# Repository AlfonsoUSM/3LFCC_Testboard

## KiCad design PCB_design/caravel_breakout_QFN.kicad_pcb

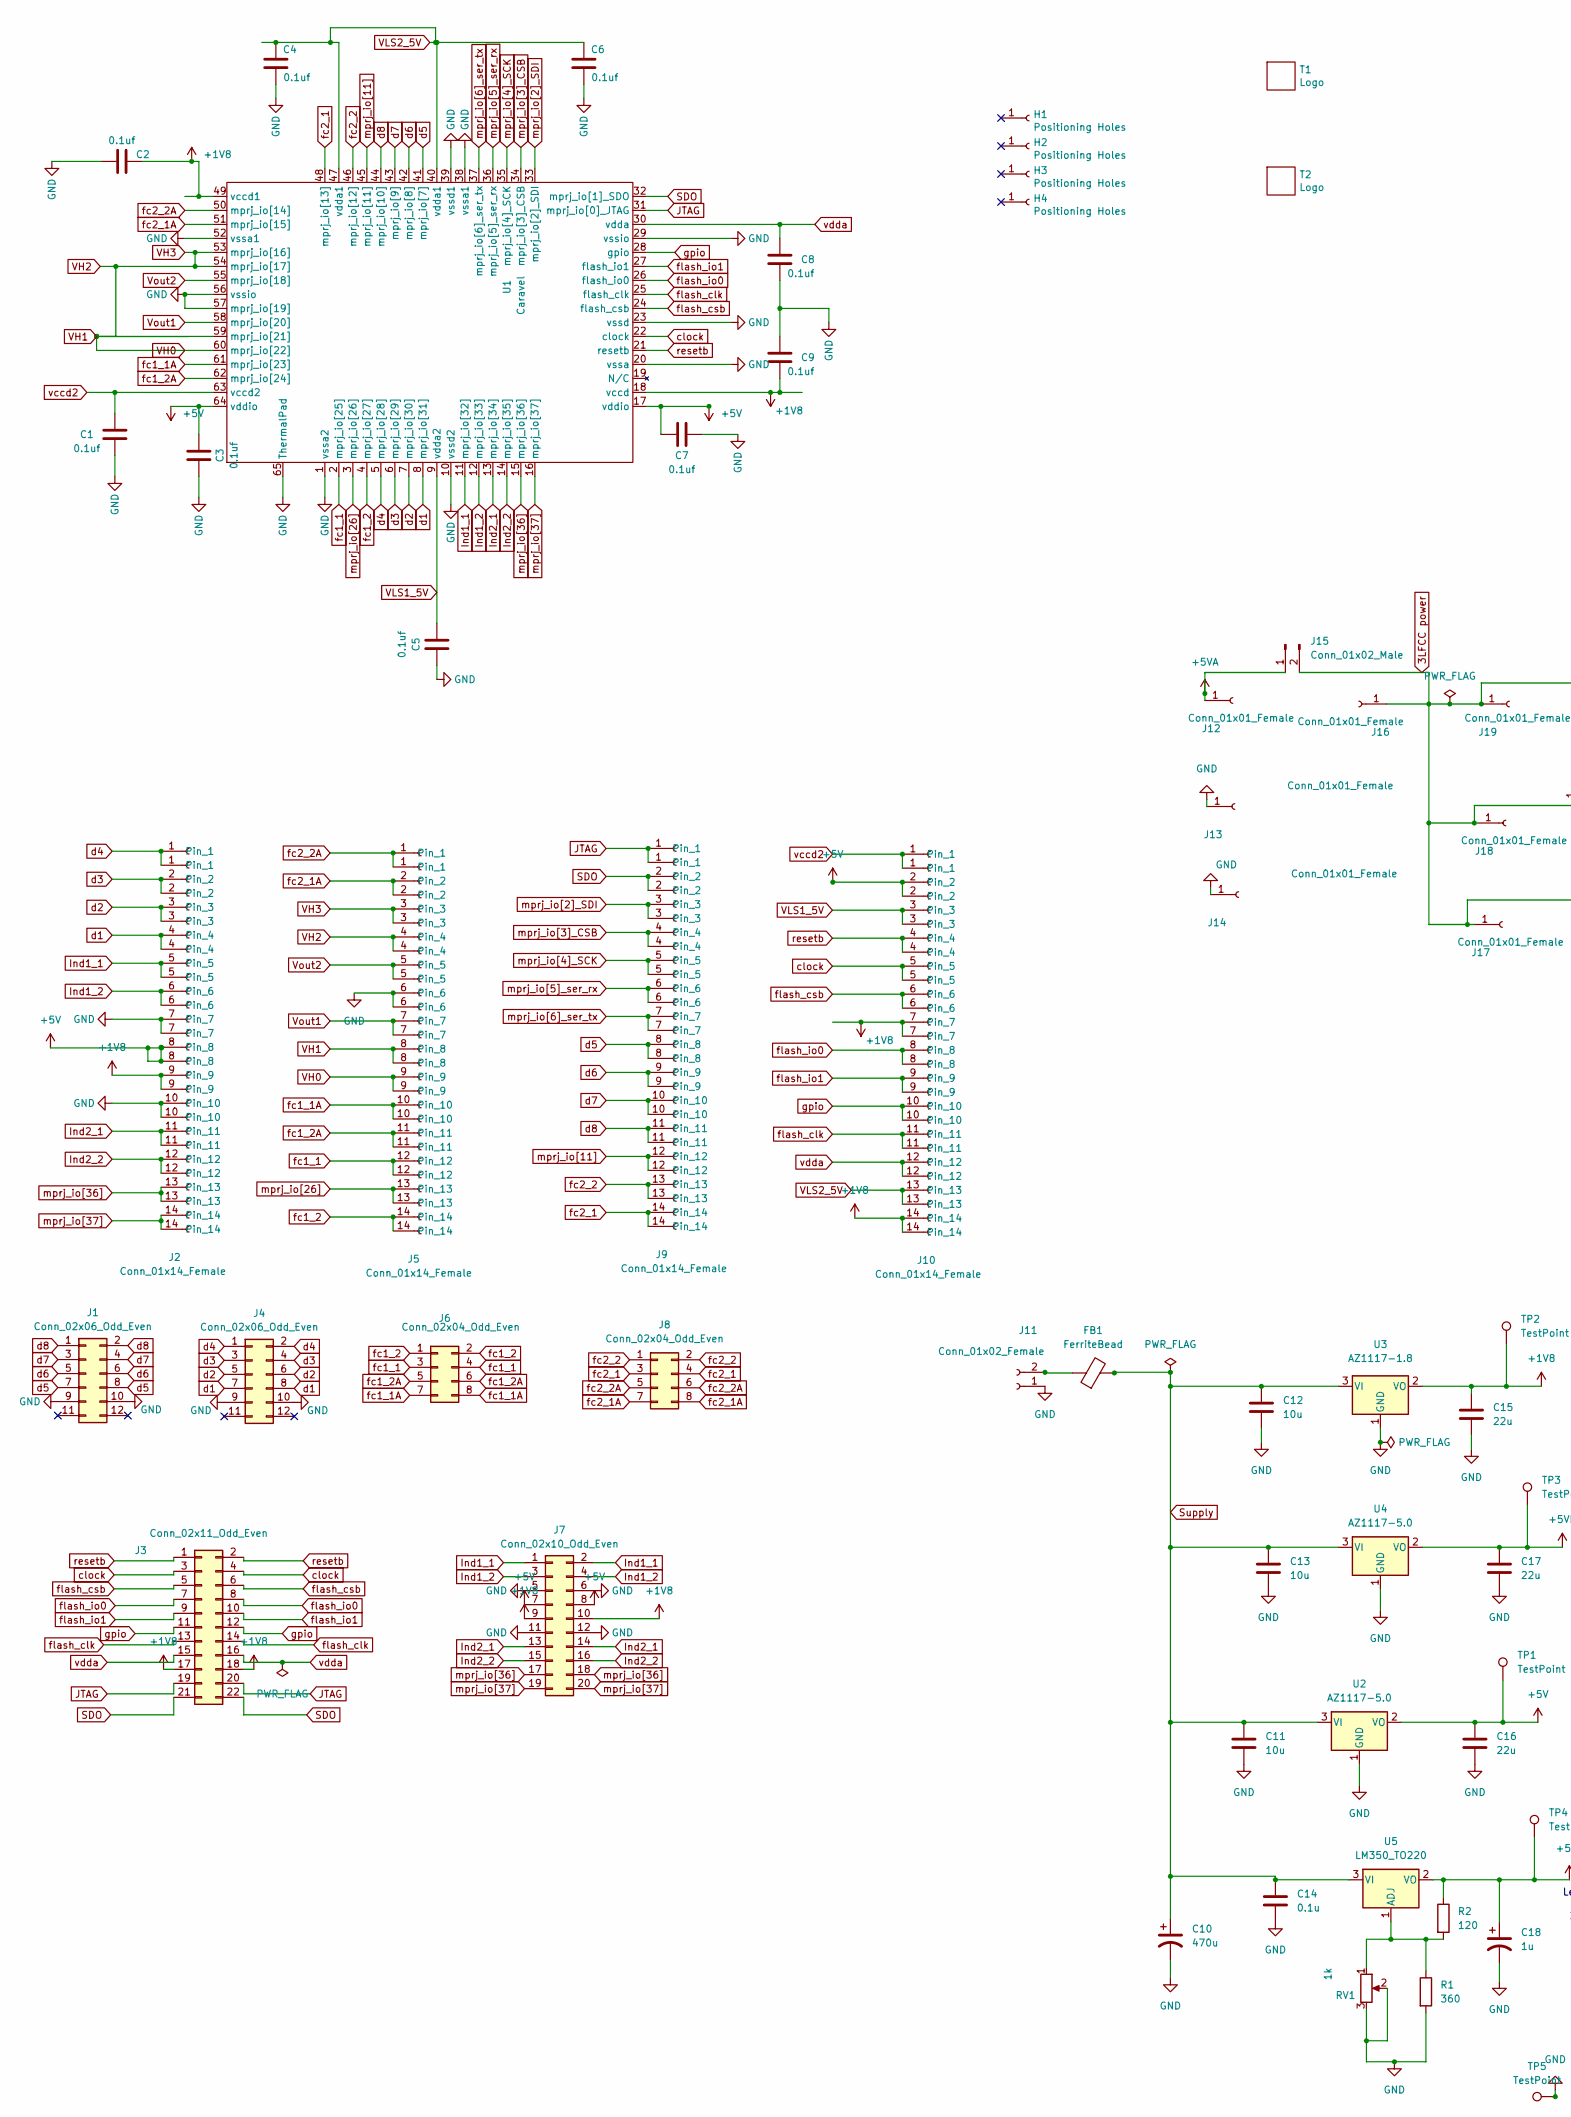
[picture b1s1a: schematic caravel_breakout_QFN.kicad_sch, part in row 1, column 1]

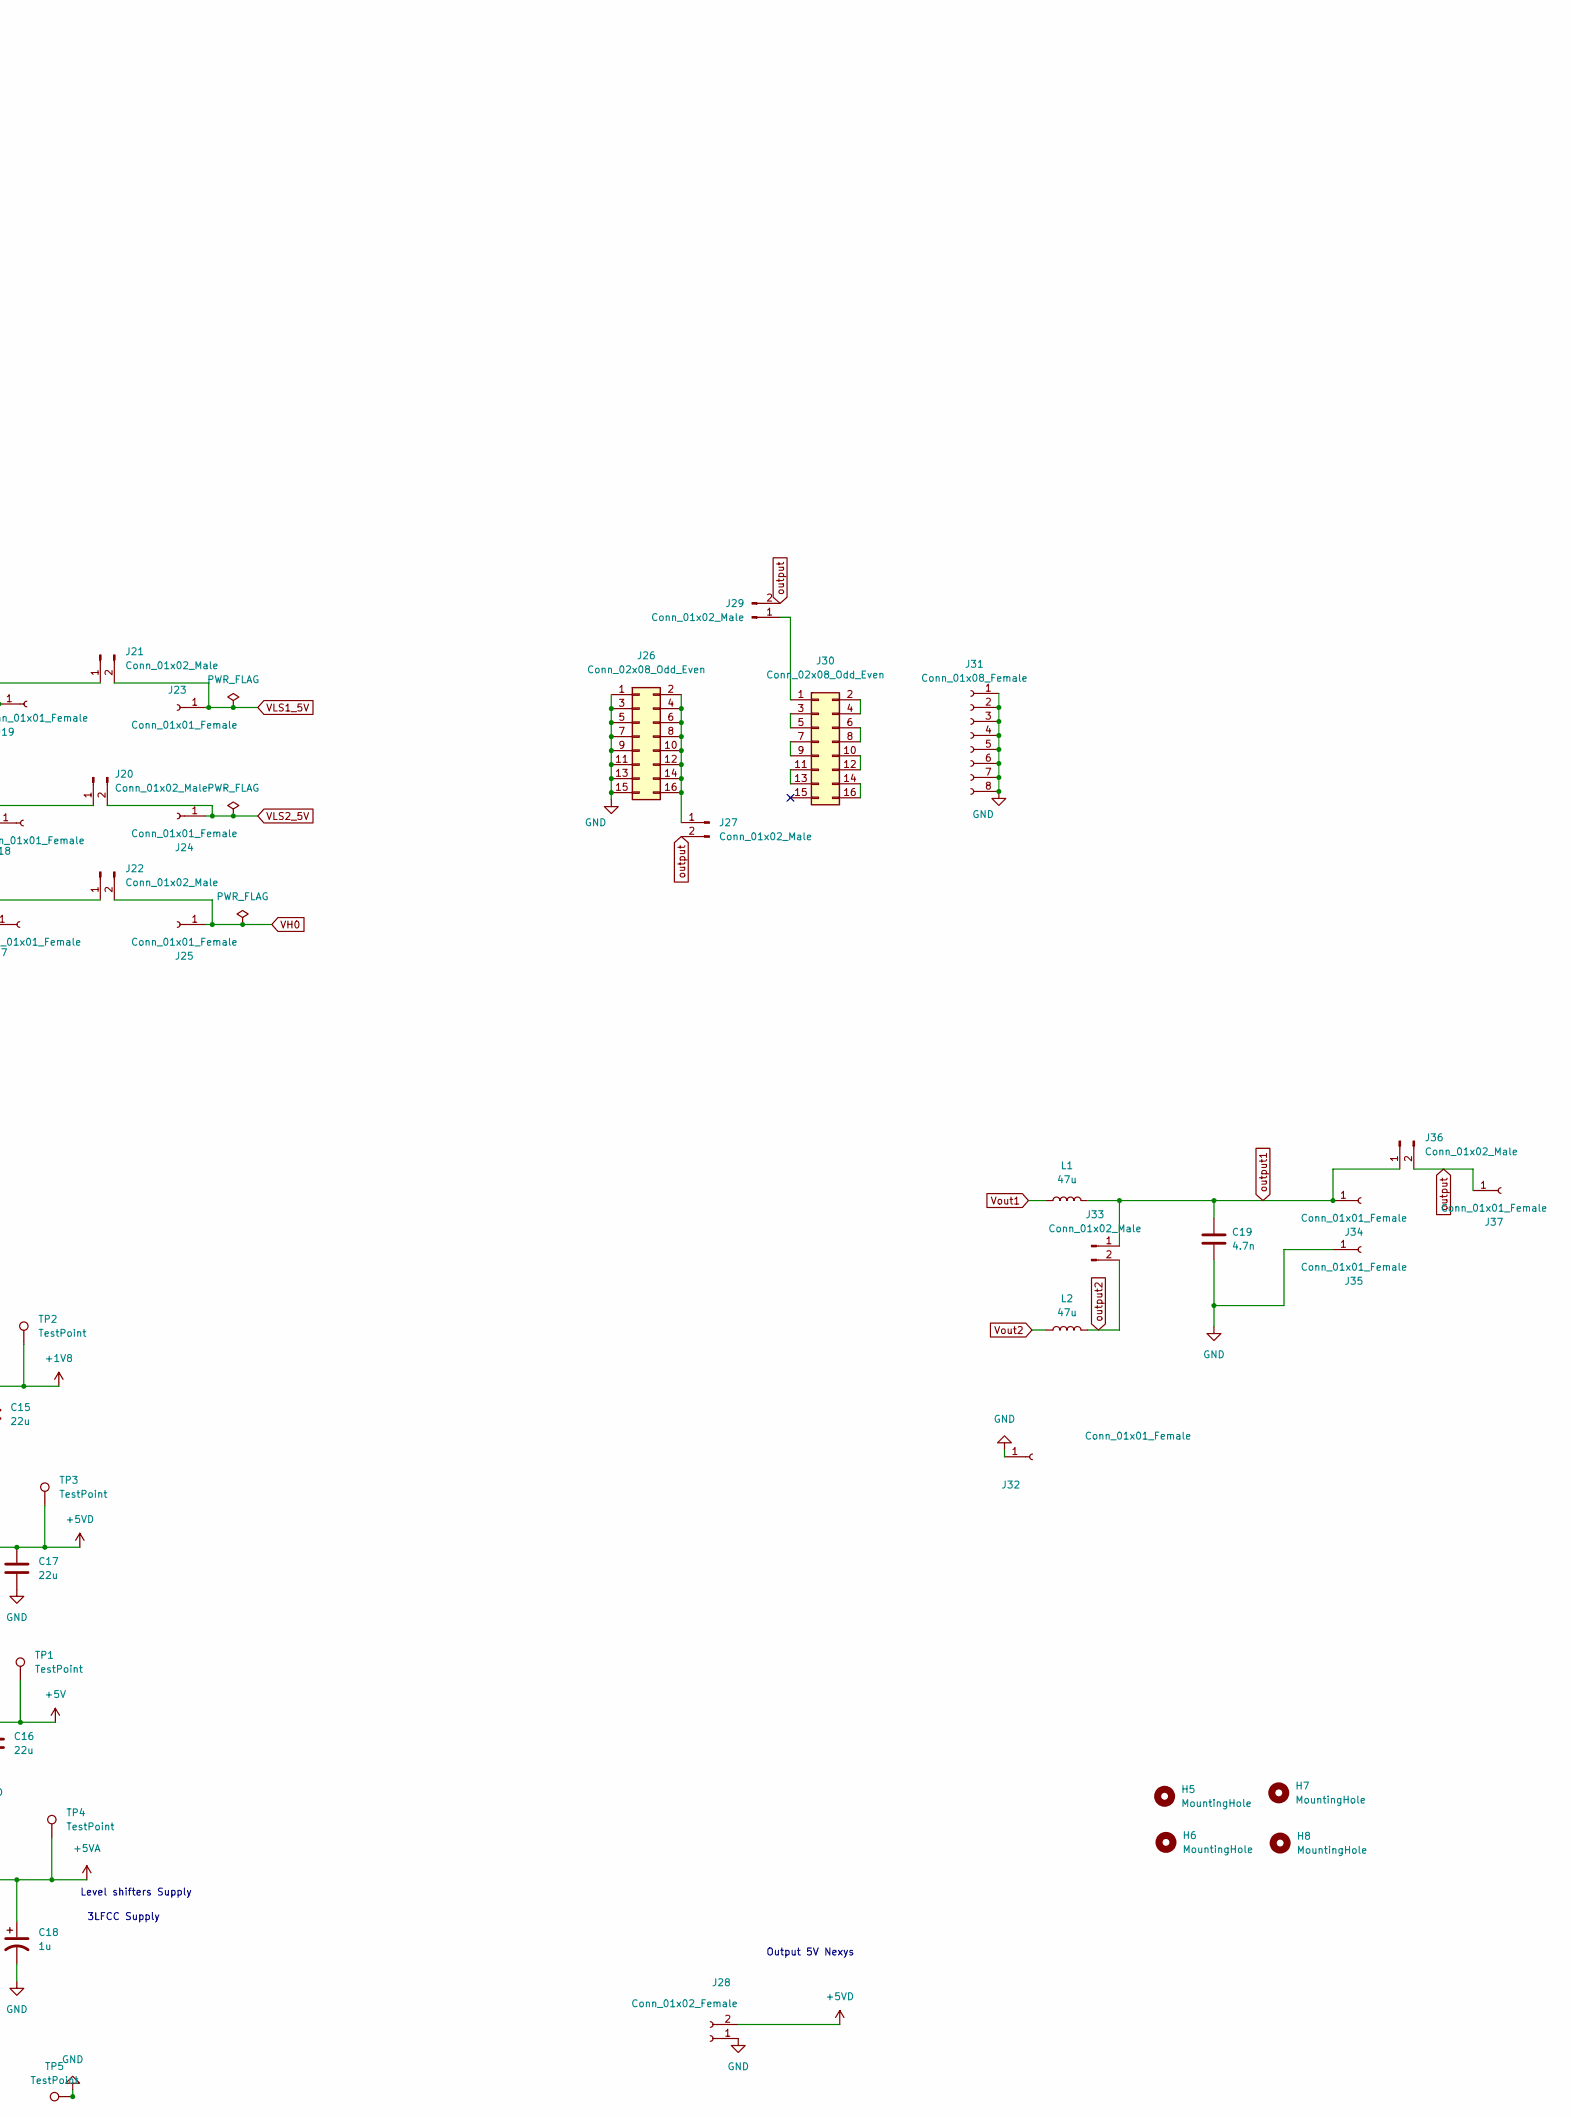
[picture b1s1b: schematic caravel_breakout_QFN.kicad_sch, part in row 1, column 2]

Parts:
C1, C2, C3, C4, C5, C6, C7, C8, C9: 0.1uf; C_0402_1005Metric
C10: 470u; CP_Radial_D10.0mm_P5.00mm
C11, C12, C13: 10u; C_1206_3216Metric
C14: 0.1u; C_1206_3216Metric_Pad1.33x1.80mm_HandSolder
C15, C16, C17: 22u; C_1206_3216Metric
C18: 1u; CP_Elec_4x3.9
C19: 4.7n; C_1206_3216Metric
FB1: FerriteBead; L_1206_3216Metric
H1, H2, H3, H4: Positioning Holes; MountingHole_2.2mm_M2_ISO7380_Pad
H5, H6, H7, H8: MountingHole; MountingHole_4mm
J1, J4: Conn_02x06_Odd_Even; PinSocket_2x06_P2.54mm_Vertical
J2, J5, J9, J10: Conn_01x14_Female; Caravel_Breakout_Connectors_2x14
J3: Conn_02x11_Odd_Even; PinHeader_2x11_P2.54mm_Vertical
J6, J8: Conn_02x04_Odd_Even; PinHeader_2x04_P2.54mm_Vertical
J7: Conn_02x10_Odd_Even; PinHeader_2x10_P2.54mm_Vertical
J11, J28: Conn_01x02_Female; TerminalBlock_bornier-2_P5.08mm
J12, J13, J14, J16, J17, J18, J19, J23, J24, J25, J32, J34, J35, J37: Conn_01x01_Female; Banana_Jack_1Pin
J15, J20, J21, J22, J27, J29, J33, J36: Conn_01x02_Male; PinHeader_1x02_P2.54mm_Vertical
J26, J30: Conn_02x08_Odd_Even; PinSocket_2x08_P2.54mm_Vertical
J31: Conn_01x08_Female; PinSocket_1x08_P2.54mm_Vertical
L1, L2: 47u; L_1210_3225Metric
R1: 360; R_1206_3216Metric
R2: 120; R_1206_3216Metric
RV1: 1k; Potentiometer_Bourns_TC33X_Vertical
T1: Logo; logo_small
T2: Logo; ef_logo
TP1, TP2, TP3, TP4, TP5: TestPoint; TestPoint_Pad_D1.5mm
U1: Caravel; QFN-64-1EP_9x9mm_P0.5mm_EP7.65x7.65mm
U2, U4: AZ1117-5.0; TO-252-2
U3: AZ1117-1.8; SOT-223-3_TabPin2
U5: LM350_TO220; TO-220-3_Vertical

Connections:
3LFCC power: J15.2, J16.1, J17.1, J18.1, J19.1, J20.1, J21.1, J22.1
+1V8: C2.2, C9.2, C15.1, J2.9, J3.17, J3.18, J7.9, J7.10, J10.7, J10.14, TP2.1, U1.18 (vccd), U1.49 (vccd1), U3.2 (VO)
+5V: C3.2, C7.2, C16.1, J2.8, J7.7, J7.8, J10.2, TP1.1, U1.17 (vddio), U1.64 (vddio), U2.2 (VO)
+5VA: C18.1, J12.1, J15.1, R2.1, TP4.1, U5.2 (VO)
+5VD: C17.1, J28.2, TP3.1, U4.2 (VO)
GND: C1.1, C2.1, C3.1, C4.2, C5.1, C6.2, C7.1, C8.2, C9.1, C10.2, C11.2, C12.2, C13.2, C14.2, C15.2, C16.2, C17.2, C18.2, C19.2, J1.9, J1.10, J2.7, J2.10, J4.9, J4.10, J5.6, J7.5, J7.6, J7.11, J7.12, J11.1, J13.1, J14.1, J26.1, J26.3, J26.5, J26.7, J26.9, J26.11, J26.13, J26.15, J28.1, J31.1, J31.2, J31.3, J31.4, J31.5, J31.6, J31.7, J31.8, J32.1, J35.1, R1.2, RV1.2, RV1.3, TP5.1, U1.1 (vssa2), U1.10 (vssd2), U1.20 (vssa), U1.23 (vssd), U1.29 (vssio), U1.38 (vssa1), U1.39 (vssd1), U1.52 (vssa1), U1.56 (vssio), U1.57 (mprj_io[19]), U1.65 (ThermalPad), U2.1 (GND), U3.1 (GND), U4.1 (GND)
Ind1_1: J2.5, J7.1, J7.2, U1.11 (mprj_io[32])
Ind1_2: J2.6, J7.3, J7.4, U1.12 (mprj_io[33])
Ind2_1: J2.11, J7.13, J7.14, U1.13 (mprj_io[34])
Ind2_2: J2.12, J7.15, J7.16, U1.14 (mprj_io[35])
JTAG: J3.19, J3.20, J9.1, U1.31 (mprj_io[0]_JTAG)
unnamed: FB1.1, J11.2
unnamed: J26.2, J26.4, J26.6, J26.8, J26.10, J26.12, J26.14, J26.16, J27.1
unnamed: J29.1, J30.1
unnamed: J30.2, J30.4
unnamed: J30.3, J30.5
unnamed: J30.6, J30.8
unnamed: J30.7, J30.9
unnamed: J30.10, J30.12
unnamed: J30.11, J30.13
unnamed: J30.14, J30.16
unnamed: R1.1, R2.2, RV1.1, U5.1 (ADJ)
SDO: J3.21, J3.22, J9.2, U1.32 (mprj_io[1]_SDO)
Supply: C10.1, C11.1, C12.1, C13.1, C14.1, FB1.2, U2.3 (VI), U3.3 (VI), U4.3 (VI), U5.3 (VI)
VH0: J5.3, J5.4, J5.8, J5.9, J22.2, J25.1, U1.53 (mprj_io[16]), U1.54 (mprj_io[17]), U1.59 (mprj_io[21]), U1.60 (mprj_io[22])
VLS1_5V: C5.2, J10.3, J21.2, J23.1, U1.9 (vdda2)
VLS2_5V: C4.1, C6.1, J10.13, J20.2, J24.1, U1.40 (vdda1), U1.47 (vdda1)
Vout1: J5.7, L1.1, U1.58 (mprj_io[20])
Vout2: J5.5, L2.1, U1.55 (mprj_io[18])
clock: J3.3, J3.4, J10.5, U1.22 (clock)
d1: J2.4, J4.7, J4.8, U1.8 (mprj_io[31])
d2: J2.3, J4.5, J4.6, U1.7 (mprj_io[30])
d3: J2.2, J4.3, J4.4, U1.6 (mprj_io[29])
d4: J2.1, J4.1, J4.2, U1.5 (mprj_io[28])
d5: J1.7, J1.8, J9.8, U1.41 (mprj_io[7])
d6: J1.5, J1.6, J9.9, U1.42 (mprj_io[8])
d7: J1.3, J1.4, J9.10, U1.43 (mprj_io[9])
d8: J1.1, J1.2, J9.11, U1.44 (mprj_io[10])
fc1_1: J5.12, J6.3, J6.4, U1.2 (mprj_io[25])
fc1_1A: J5.10, J6.7, J6.8, U1.61 (mprj_io[23])
fc1_2: J5.14, J6.1, J6.2, U1.4 (mprj_io[27])
fc1_2A: J5.11, J6.5, J6.6, U1.62 (mprj_io[24])
fc2_1: J8.3, J8.4, J9.14, U1.48 (mprj_io[13])
fc2_1A: J5.2, J8.7, J8.8, U1.51 (mprj_io[15])
fc2_2: J8.1, J8.2, J9.13, U1.46 (mprj_io[12])
fc2_2A: J5.1, J8.5, J8.6, U1.50 (mprj_io[14])
flash_clk: J3.13, J3.14, J10.11, U1.25 (flash_clk)
flash_csb: J3.5, J3.6, J10.6, U1.24 (flash_csb)
flash_io0: J3.7, J3.8, J10.8, U1.26 (flash_io0)
flash_io1: J3.9, J3.10, J10.9, U1.27 (flash_io1)
gpio: J3.11, J3.12, J10.10, U1.28 (gpio)
mprj_io[2]_SDI: J9.3, U1.33 (mprj_io[2]_SDI)
mprj_io[3]_CSB: J9.4, U1.34 (mprj_io[3]_CSB)
mprj_io[4]_SCK: J9.5, U1.35 (mprj_io[4]_SCK)
mprj_io[5]_ser_rx: J9.6, U1.36 (mprj_io[5]_ser_rx)
mprj_io[6]_ser_tx: J9.7, U1.37 (mprj_io[6]_ser_tx)
mprj_io[11]: J9.12, U1.45 (mprj_io[11])
mprj_io[26]: J5.13, U1.3 (mprj_io[26])
mprj_io[36]: J2.13, J7.17, J7.18, U1.15 (mprj_io[36])
mprj_io[37]: J2.14, J7.19, J7.20, U1.16 (mprj_io[37])
output: J27.2, J29.2, J36.2, J37.1
output1: C19.1, J33.1, J34.1, J36.1, L1.2
output2: J33.2, L2.2
resetb: J3.1, J3.2, J10.4, U1.21 (resetb)
vccd2: C1.2, J10.1, U1.63 (vccd2)
vdda: C8.1, J3.15, J3.16, J10.12, U1.30 (vdda)

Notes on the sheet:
Level shifters Supply
3LFCC Supply
Output 5V Nexys

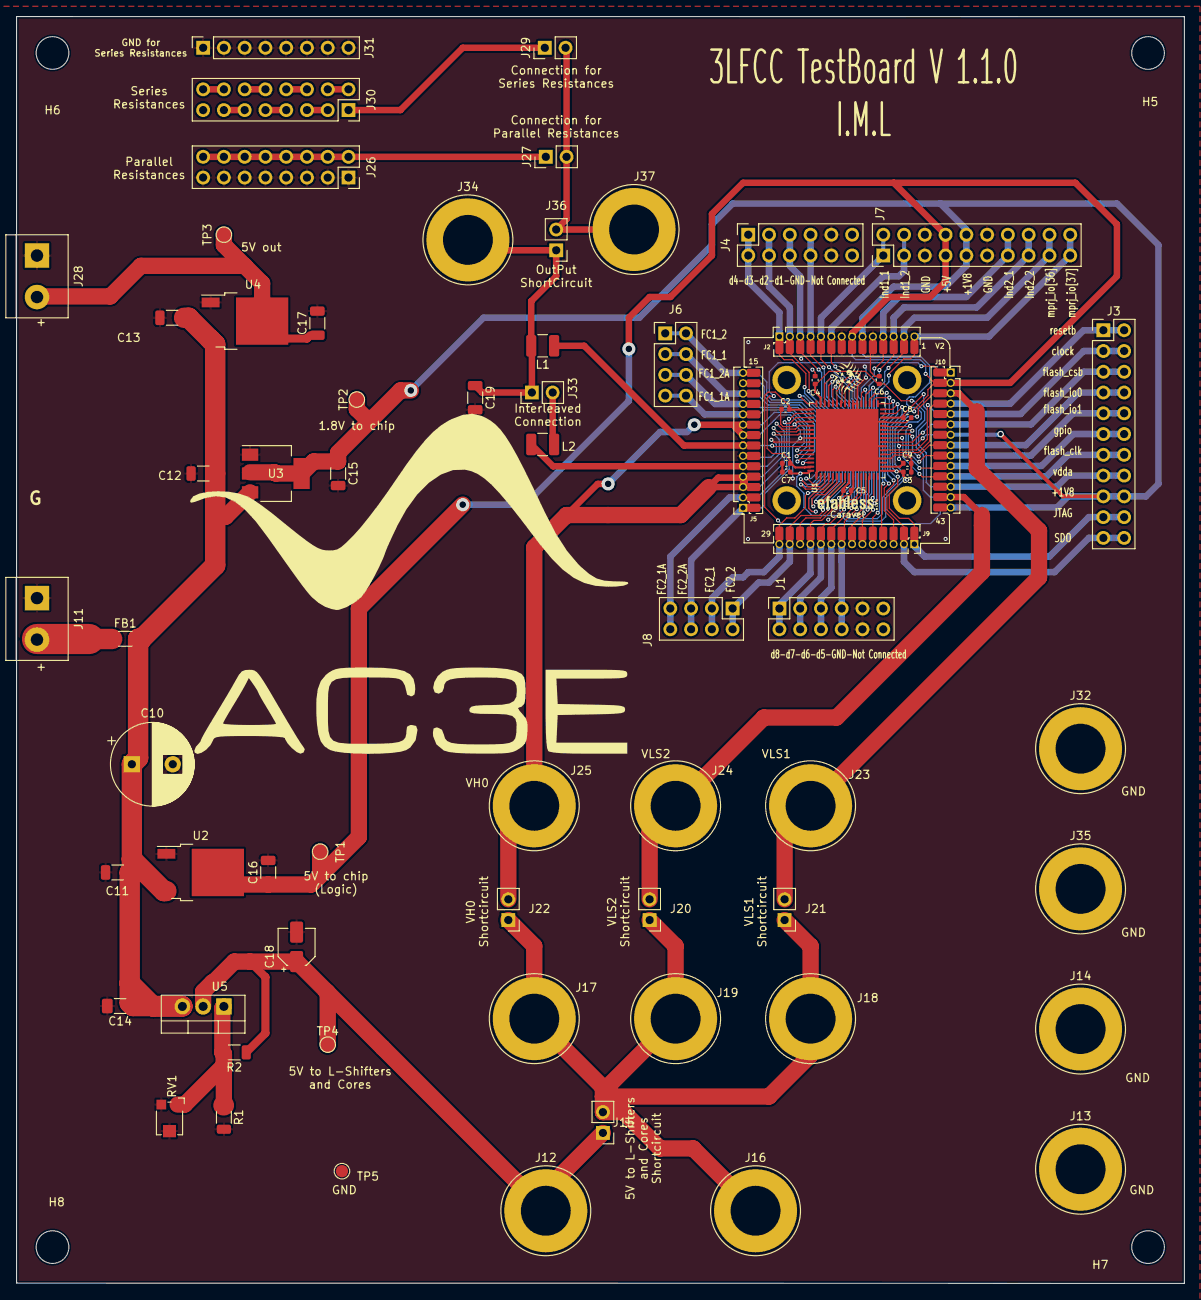
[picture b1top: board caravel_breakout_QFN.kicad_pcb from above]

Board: 2 copper layers, 142.8 x 155.0 mm, 83 parts (0 on the bottom side), 66 nets.

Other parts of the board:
G: LOGO; AC3Efootprint

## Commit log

2023-02-20 Uploaded Test plan
2023-02-20 PWM generation
    For Nexys 7 FPGA
2023-02-20 PCB version 1.1.1
    Pcb based in Efabless Breakout Board
2023-02-20 PCB version 1.1.2
    Added level shifters for control pins (3V3 to 1V8).
2023-02-21 Commented code
2023-02-21 Uploaded design
    1st PCB design
2023-11-14 Multiple changes
    Erased Files Like testplans and updated Bitstreams to the latest ones
2023-11-14 Revert "Multiple changes"
    This reverts commit 5ac29041cd4e4eb42e213be6e1388a64195ca9ec.
2023-11-14 Added bitsreams for FPGA
    Added to bitstream to test the 3LFCC with the FPGA and the documentation
2023-11-14 Added TestBoard User Manual
2023-11-14 added 1MHz(25%/50%75%)
